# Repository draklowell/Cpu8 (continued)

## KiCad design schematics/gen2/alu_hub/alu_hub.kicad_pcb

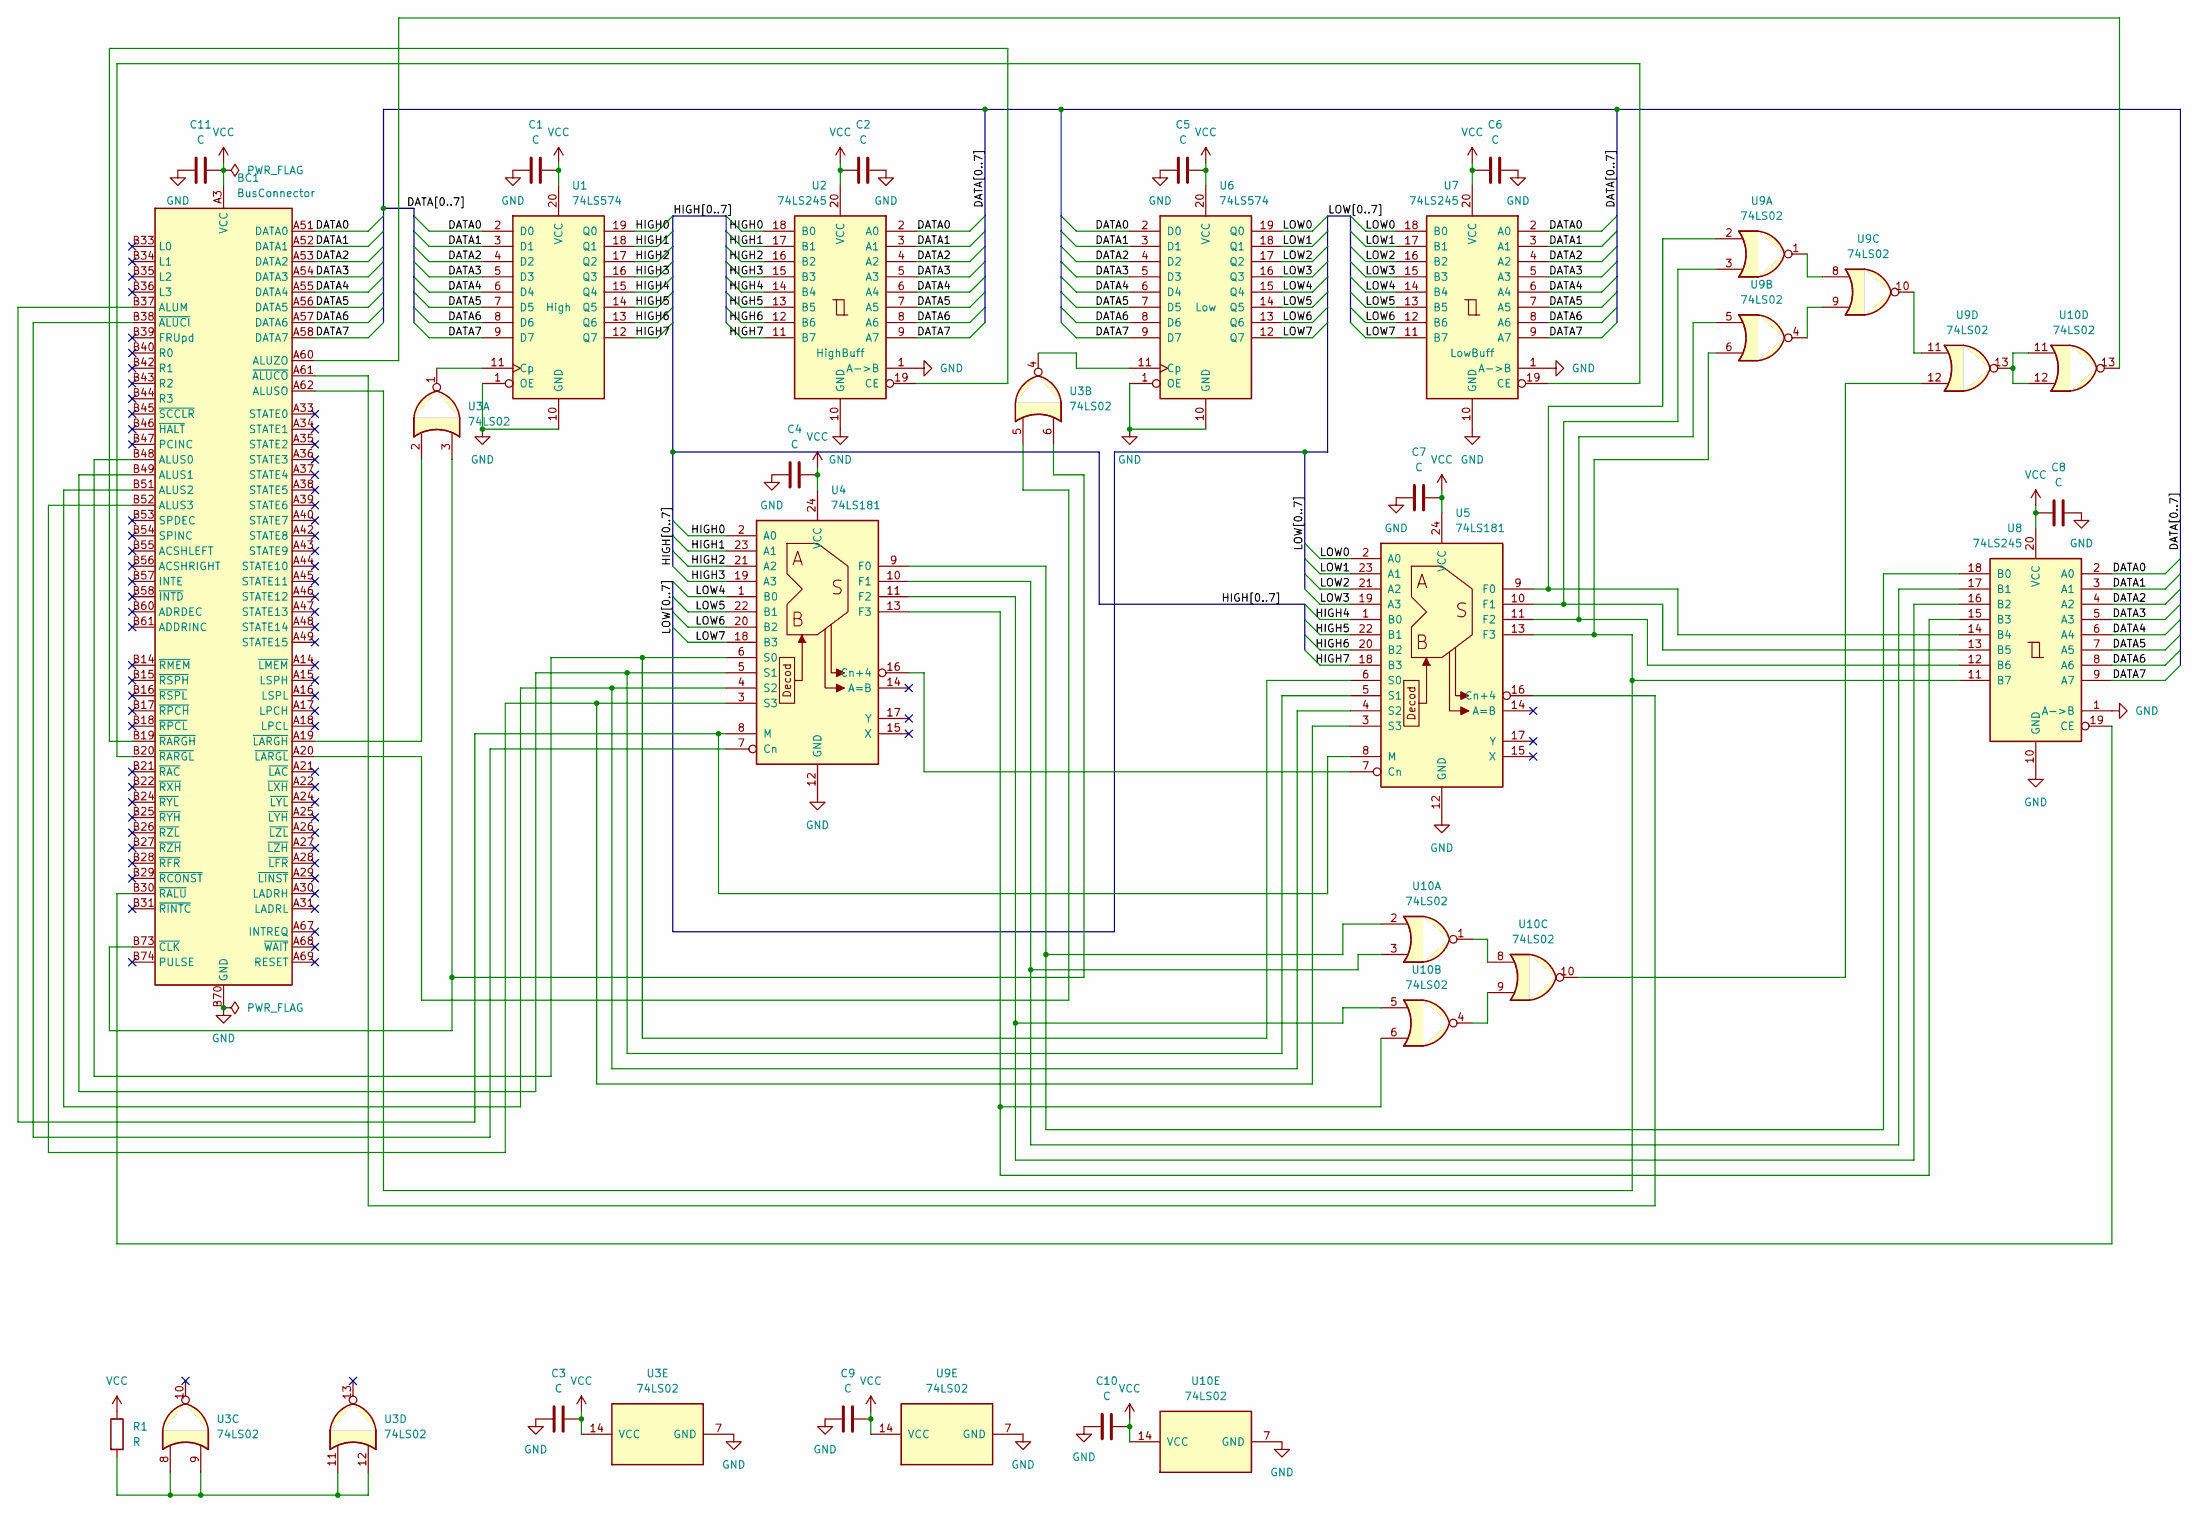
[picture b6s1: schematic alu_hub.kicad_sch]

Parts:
BC1: BusConnector; BUS_PCIexpress_x16
C1, C2, C3, C5, C6, C7, C8, C9, C10: C; C_Disc_D3.0mm_W1.6mm_P2.50mm
C4: C; C_Disc_D5.0mm_W2.5mm_P5.00mm
C11: C; C_Radial_D6.3mm_H5.0mm_P2.50mm
R1: R; R_Axial_DIN0207_L6.3mm_D2.5mm_P7.62mm_Horizontal
U1, U6: 74LS574; DIP-20_W7.62mm_Socket_LongPads
U2, U7, U8: 74LS245; DIP-20_W7.62mm_Socket_LongPads
U3, U9, U10: 74LS02; DIP-14_W7.62mm_Socket_LongPads
U4, U5: 74LS181; DIP-24_W15.24mm_Socket_LongPads

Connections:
/DATA0: BC1.A51 (DATA0), U1.2 (D0), U2.2 (A0), U6.2 (D0), U7.2 (A0), U8.2 (A0)
/DATA1: BC1.A52 (DATA1), U1.3 (D1), U2.3 (A1), U6.3 (D1), U7.3 (A1), U8.3 (A1)
/DATA2: BC1.A53 (DATA2), U1.4 (D2), U2.4 (A2), U6.4 (D2), U7.4 (A2), U8.4 (A2)
/DATA3: BC1.A54 (DATA3), U1.5 (D3), U2.5 (A3), U6.5 (D3), U7.5 (A3), U8.5 (A3)
/DATA4: BC1.A55 (DATA4), U1.6 (D4), U2.6 (A4), U6.6 (D4), U7.6 (A4), U8.6 (A4)
/DATA5: BC1.A56 (DATA5), U1.7 (D5), U2.7 (A5), U6.7 (D5), U7.7 (A5), U8.7 (A5)
/DATA6: BC1.A57 (DATA6), U1.8 (D6), U2.8 (A6), U6.8 (D6), U7.8 (A6), U8.8 (A6)
/DATA7: BC1.A58 (DATA7), U1.9 (D7), U2.9 (A7), U6.9 (D7), U7.9 (A7), U8.9 (A7)
/HIGH0: U1.19 (Q0), U2.18 (B0), U4.2 (A0)
/HIGH1: U1.18 (Q1), U2.17 (B1), U4.23 (A1)
/HIGH2: U1.17 (Q2), U2.16 (B2), U4.21 (A2)
/HIGH3: U1.16 (Q3), U2.15 (B3), U4.19 (A3)
/HIGH4: U1.15 (Q4), U2.14 (B4), U5.1 (B0)
/HIGH5: U1.14 (Q5), U2.13 (B5), U5.22 (B1)
/HIGH6: U1.13 (Q6), U2.12 (B6), U5.20 (B2)
/HIGH7: U1.12 (Q7), U2.11 (B7), U5.18 (B3)
/LOW0: U5.2 (A0), U6.19 (Q0), U7.18 (B0)
/LOW1: U5.23 (A1), U6.18 (Q1), U7.17 (B1)
/LOW2: U5.21 (A2), U6.17 (Q2), U7.16 (B2)
/LOW3: U5.19 (A3), U6.16 (Q3), U7.15 (B3)
/LOW4: U4.1 (B0), U6.15 (Q4), U7.14 (B4)
/LOW5: U4.22 (B1), U6.14 (Q5), U7.13 (B5)
/LOW6: U4.20 (B2), U6.13 (Q6), U7.12 (B6)
/LOW7: U4.18 (B3), U6.12 (Q7), U7.11 (B7)
GND: BC1.A12 (GND), BC1.A13 (GND), BC1.A23 (GND), BC1.A32 (GND), BC1.A41 (GND), BC1.A50 (GND), BC1.A59 (GND), BC1.A63 (GND), BC1.A64 (GND), BC1.A65 (GND), BC1.A66 (GND), BC1.A70 (GND), BC1.A71 (GND), BC1.A72 (GND), BC1.A73 (GND), BC1.A74 (GND), BC1.A75 (GND), BC1.A76 (GND), BC1.B12 (GND), BC1.B13 (GND), BC1.B23 (GND), BC1.B32 (GND), BC1.B41 (GND), BC1.B50 (GND), BC1.B59 (GND), BC1.B62 (GND), BC1.B63 (GND), BC1.B64 (GND), BC1.B65 (GND), BC1.B66 (GND), BC1.B67 (GND), BC1.B68 (GND), BC1.B69 (GND), BC1.B70 (GND), BC1.B71 (GND), BC1.B72 (GND), BC1.B75 (GND), BC1.B76 (GND), C1.1, C2.1, C3.1, C4.1, C5.1, C6.1, C7.1, C8.1, C9.1, C10.1, C11.1, U1.1 (OE), U1.10 (GND), U2.1 (A->B), U2.10 (GND), U3.7 (GND), U4.12 (GND), U5.12 (GND), U6.1 (OE), U6.10 (GND), U7.1 (A->B), U7.10 (GND), U8.1 (A->B), U8.10 (GND), U9.7 (GND), U10.7 (GND)
unnamed: BC1.B37 (ALUM), U4.8 (M), U5.8 (M)
unnamed: BC1.B48 (ALUS0), U4.6 (S0), U5.6 (S0)
unnamed: BC1.B49 (ALUS1), U4.5 (S1), U5.5 (S1)
unnamed: BC1.B51 (ALUS2), U4.4 (S2), U5.4 (S2)
unnamed: BC1.B52 (ALUS3), U4.3 (S3), U5.3 (S3)
unnamed: BC1.A62 (ALUSO), U5.13 (F3), U8.11 (B7), U9.6
unnamed: BC1.A60 (ALUZO), U10.13
unnamed: BC1.B38 (~ALUCI), U4.7 (Cn)
unnamed: BC1.A61 (~ALUCO), U5.16 (Cn+4)
unnamed: BC1.B73 (~CLK), U3.3, U3.6
unnamed: BC1.A19 (~LARGH), U3.2
unnamed: BC1.A20 (~LARGL), U3.5
unnamed: BC1.B30 (~RALU), U8.19 (CE)
unnamed: BC1.B19 (~RARGH), U2.19 (CE)
unnamed: BC1.B20 (~RARGL), U7.19 (CE)
unnamed: R1.2, U3.8, U3.9, U3.11, U3.12
unnamed: U1.11 (Cp), U3.1
unnamed: U4.16 (Cn+4), U5.7 (Cn)
unnamed: U4.9 (F0), U8.18 (B0), U10.2
unnamed: U4.10 (F1), U8.17 (B1), U10.3
unnamed: U4.11 (F2), U8.16 (B2), U10.5
unnamed: U4.13 (F3), U8.15 (B3), U10.6
unnamed: U5.9 (F0), U8.14 (B4), U9.2
unnamed: U5.10 (F1), U8.13 (B5), U9.3
unnamed: U5.11 (F2), U8.12 (B6), U9.5
unnamed: U3.4, U6.11 (Cp)
unnamed: U9.1, U9.8
unnamed: U9.4, U9.9
unnamed: U9.10, U9.11
unnamed: U10.1, U10.8
unnamed: U10.4, U10.9
unnamed: U9.12, U10.10
unnamed: U9.13, U10.11, U10.12
VCC: BC1.A1 (VCC), BC1.A2 (VCC), BC1.A3 (VCC), BC1.A4 (VCC), BC1.A5 (VCC), BC1.B1 (VCC), BC1.B2 (VCC), BC1.B3 (VCC), BC1.B4 (VCC), BC1.B5 (VCC), C1.2, C2.2, C3.2, C4.2, C5.2, C6.2, C7.2, C8.2, C9.2, C10.2, C11.2, R1.1, U1.20 (VCC), U2.20 (VCC), U3.14 (VCC), U4.24 (VCC), U5.24 (VCC), U6.20 (VCC), U7.20 (VCC), U8.20 (VCC), U9.14 (VCC), U10.14 (VCC)

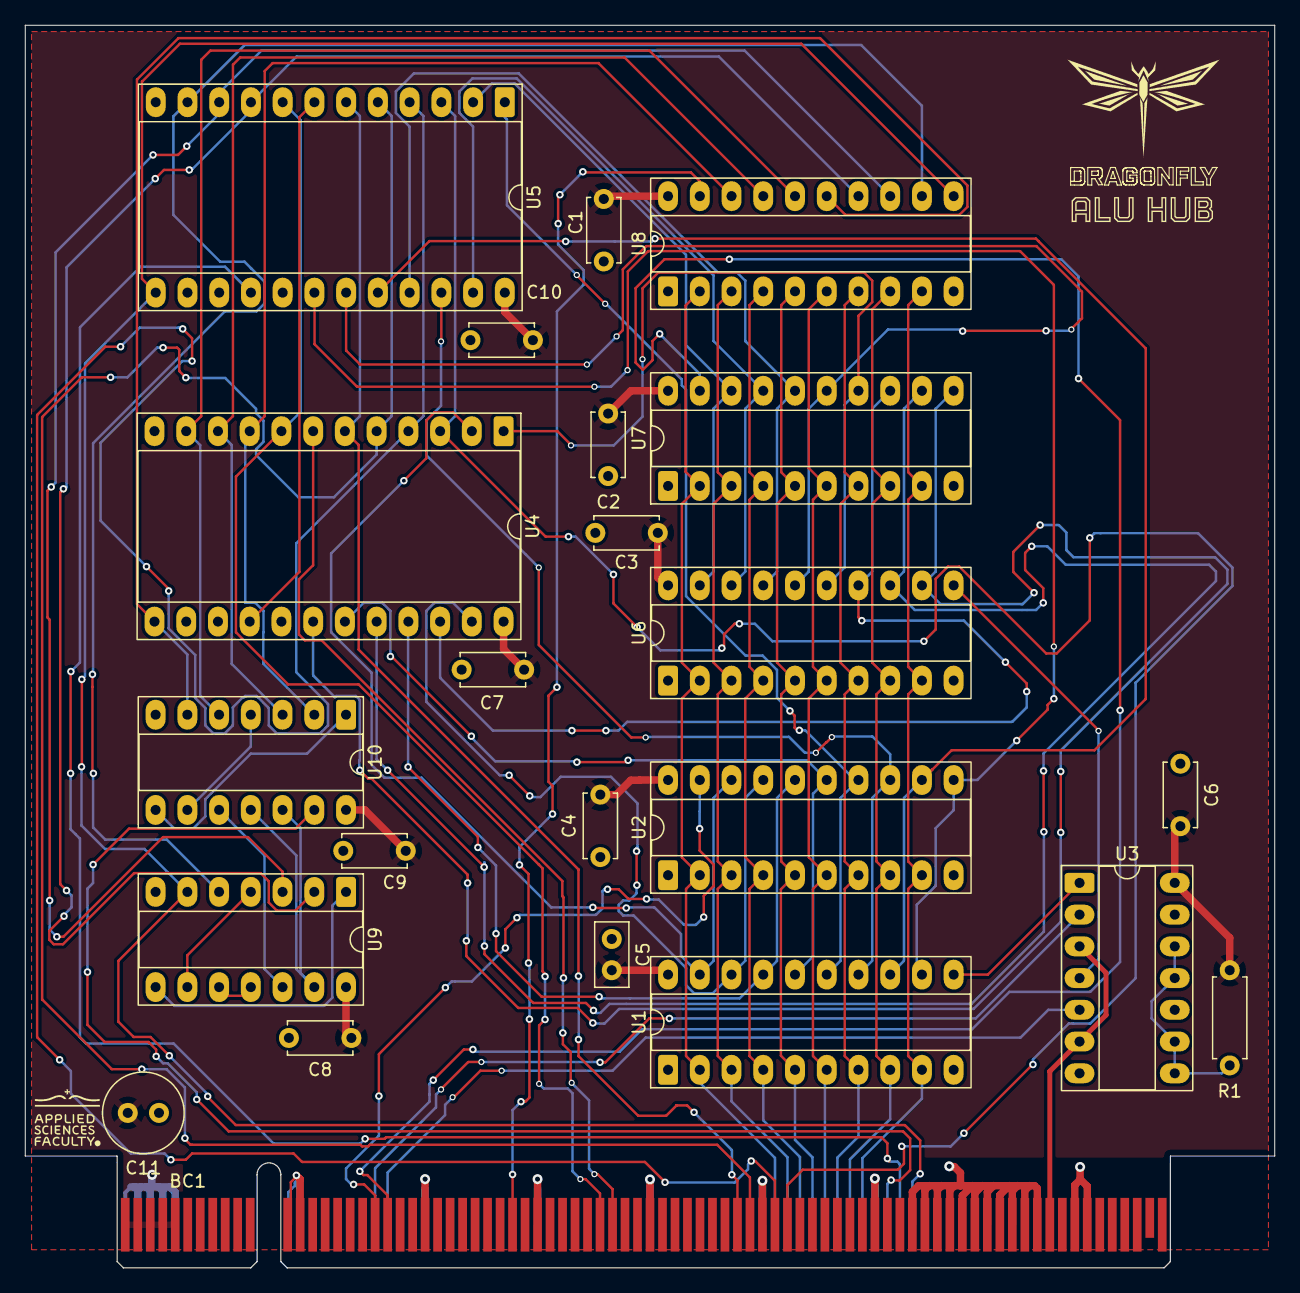
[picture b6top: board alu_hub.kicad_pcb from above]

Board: 2 copper layers, 100.0 x 99.4 mm, 24 parts (0 on the bottom side), 59 nets.

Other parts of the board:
kibuzzard-6911C7CA: G***; kibuzzard-6911C7CA

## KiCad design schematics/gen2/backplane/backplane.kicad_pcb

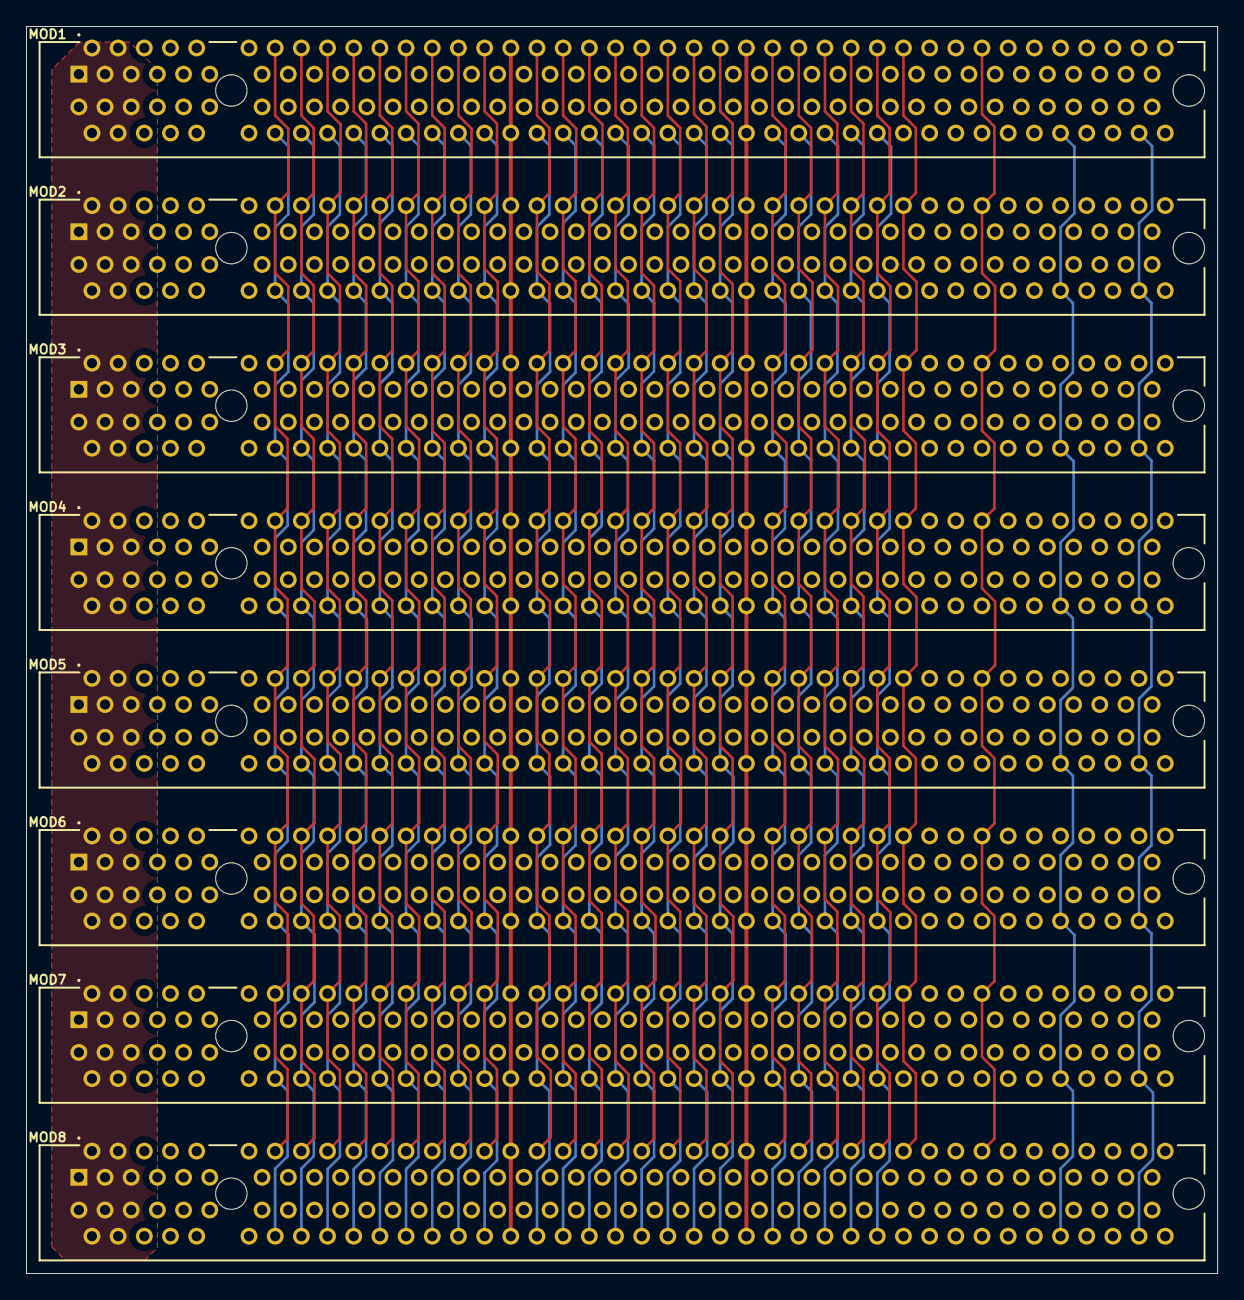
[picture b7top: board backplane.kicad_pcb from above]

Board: 4 copper layers, 91.0 x 95.3 mm, 8 parts (0 on the bottom side), 97 nets.

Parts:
MOD1, MOD2, MOD3, MOD4, MOD5, MOD6, MOD7, MOD8: Module; BusSlot

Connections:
/ACSHLEFT: MOD1.B55 (ACSHLEFT), MOD2.B55 (ACSHLEFT), MOD3.B55 (ACSHLEFT), MOD4.B55 (ACSHLEFT), MOD5.B55 (ACSHLEFT), MOD6.B55 (ACSHLEFT), MOD7.B55 (ACSHLEFT), MOD8.B55 (ACSHLEFT)
/ACSHRIGHT: MOD1.B56 (ACSHRIGHT), MOD2.B56 (ACSHRIGHT), MOD3.B56 (ACSHRIGHT), MOD4.B56 (ACSHRIGHT), MOD5.B56 (ACSHRIGHT), MOD6.B56 (ACSHRIGHT), MOD7.B56 (ACSHRIGHT), MOD8.B56 (ACSHRIGHT)
/ADRDEC: MOD1.B60 (ADRDEC), MOD2.B60 (ADRDEC), MOD3.B60 (ADRDEC), MOD4.B60 (ADRDEC), MOD5.B60 (ADRDEC), MOD6.B60 (ADRDEC), MOD7.B60 (ADRDEC), MOD8.B60 (ADRDEC)
/ADRINC: MOD1.B61 (ADDRINC), MOD2.B61 (ADDRINC), MOD3.B61 (ADDRINC), MOD4.B61 (ADDRINC), MOD5.B61 (ADDRINC), MOD6.B61 (ADDRINC), MOD7.B61 (ADDRINC), MOD8.B61 (ADDRINC)
/ALUM: MOD1.B37 (ALUM), MOD2.B37 (ALUM), MOD3.B37 (ALUM), MOD4.B37 (ALUM), MOD5.B37 (ALUM), MOD6.B37 (ALUM), MOD7.B37 (ALUM), MOD8.B37 (ALUM)
/ALUS0: MOD1.B48 (ALUS0), MOD2.B48 (ALUS0), MOD3.B48 (ALUS0), MOD4.B48 (ALUS0), MOD5.B48 (ALUS0), MOD6.B48 (ALUS0), MOD7.B48 (ALUS0), MOD8.B48 (ALUS0)
/ALUS1: MOD1.B49 (ALUS1), MOD2.B49 (ALUS1), MOD3.B49 (ALUS1), MOD4.B49 (ALUS1), MOD5.B49 (ALUS1), MOD6.B49 (ALUS1), MOD7.B49 (ALUS1), MOD8.B49 (ALUS1)
/ALUS2: MOD1.B51 (ALUS2), MOD2.B51 (ALUS2), MOD3.B51 (ALUS2), MOD4.B51 (ALUS2), MOD5.B51 (ALUS2), MOD6.B51 (ALUS2), MOD7.B51 (ALUS2), MOD8.B51 (ALUS2)
/ALUS3: MOD1.B52 (ALUS3), MOD2.B52 (ALUS3), MOD3.B52 (ALUS3), MOD4.B52 (ALUS3), MOD5.B52 (ALUS3), MOD6.B52 (ALUS3), MOD7.B52 (ALUS3), MOD8.B52 (ALUS3)
/ALUSO: MOD1.A62 (ALUSO), MOD2.A62 (ALUSO), MOD3.A62 (ALUSO), MOD4.A62 (ALUSO), MOD5.A62 (ALUSO), MOD6.A62 (ALUSO), MOD7.A62 (ALUSO), MOD8.A62 (ALUSO)
/ALUZO: MOD1.A60 (ALUZO), MOD2.A60 (ALUZO), MOD3.A60 (ALUZO), MOD4.A60 (ALUZO), MOD5.A60 (ALUZO), MOD6.A60 (ALUZO), MOD7.A60 (ALUZO), MOD8.A60 (ALUZO)
/DATA0: MOD1.A51 (DATA0), MOD2.A51 (DATA0), MOD3.A51 (DATA0), MOD4.A51 (DATA0), MOD5.A51 (DATA0), MOD6.A51 (DATA0), MOD7.A51 (DATA0), MOD8.A51 (DATA0)
/DATA1: MOD1.A52 (DATA1), MOD2.A52 (DATA1), MOD3.A52 (DATA1), MOD4.A52 (DATA1), MOD5.A52 (DATA1), MOD6.A52 (DATA1), MOD7.A52 (DATA1), MOD8.A52 (DATA1)
/DATA2: MOD1.A53 (DATA2), MOD2.A53 (DATA2), MOD3.A53 (DATA2), MOD4.A53 (DATA2), MOD5.A53 (DATA2), MOD6.A53 (DATA2), MOD7.A53 (DATA2), MOD8.A53 (DATA2)
/DATA3: MOD1.A54 (DATA3), MOD2.A54 (DATA3), MOD3.A54 (DATA3), MOD4.A54 (DATA3), MOD5.A54 (DATA3), MOD6.A54 (DATA3), MOD7.A54 (DATA3), MOD8.A54 (DATA3)
/DATA4: MOD1.A55 (DATA4), MOD2.A55 (DATA4), MOD3.A55 (DATA4), MOD4.A55 (DATA4), MOD5.A55 (DATA4), MOD6.A55 (DATA4), MOD7.A55 (DATA4), MOD8.A55 (DATA4)
/DATA5: MOD1.A56 (DATA5), MOD2.A56 (DATA5), MOD3.A56 (DATA5), MOD4.A56 (DATA5), MOD5.A56 (DATA5), MOD6.A56 (DATA5), MOD7.A56 (DATA5), MOD8.A56 (DATA5)
/DATA6: MOD1.A57 (DATA6), MOD2.A57 (DATA6), MOD3.A57 (DATA6), MOD4.A57 (DATA6), MOD5.A57 (DATA6), MOD6.A57 (DATA6), MOD7.A57 (DATA6), MOD8.A57 (DATA6)
/DATA7: MOD1.A58 (DATA7), MOD2.A58 (DATA7), MOD3.A58 (DATA7), MOD4.A58 (DATA7), MOD5.A58 (DATA7), MOD6.A58 (DATA7), MOD7.A58 (DATA7), MOD8.A58 (DATA7)
/FRUpd: MOD1.B39 (FRUpd), MOD2.B39 (FRUpd), MOD3.B39 (FRUpd), MOD4.B39 (FRUpd), MOD5.B39 (FRUpd), MOD6.B39 (FRUpd), MOD7.B39 (FRUpd), MOD8.B39 (FRUpd)
/INTE: MOD1.B57 (INTE), MOD2.B57 (INTE), MOD3.B57 (INTE), MOD4.B57 (INTE), MOD5.B57 (INTE), MOD6.B57 (INTE), MOD7.B57 (INTE), MOD8.B57 (INTE)
/INTREQ: MOD1.A67 (INTREQ), MOD2.A67 (INTREQ), MOD3.A67 (INTREQ), MOD4.A67 (INTREQ), MOD5.A67 (INTREQ), MOD6.A67 (INTREQ), MOD7.A67 (INTREQ), MOD8.A67 (INTREQ)
/L0: MOD1.B33 (L0), MOD2.B33 (L0), MOD3.B33 (L0), MOD4.B33 (L0), MOD5.B33 (L0), MOD6.B33 (L0), MOD7.B33 (L0), MOD8.B33 (L0)
/L1: MOD1.B34 (L1), MOD2.B34 (L1), MOD3.B34 (L1), MOD4.B34 (L1), MOD5.B34 (L1), MOD6.B34 (L1), MOD7.B34 (L1), MOD8.B34 (L1)
/L2: MOD1.B35 (L2), MOD2.B35 (L2), MOD3.B35 (L2), MOD4.B35 (L2), MOD5.B35 (L2), MOD6.B35 (L2), MOD7.B35 (L2), MOD8.B35 (L2)
/L3: MOD1.B36 (L3), MOD2.B36 (L3), MOD3.B36 (L3), MOD4.B36 (L3), MOD5.B36 (L3), MOD6.B36 (L3), MOD7.B36 (L3), MOD8.B36 (L3)
/L4: MOD1.B79 (L4), MOD2.B79 (L4), MOD3.B79 (L4), MOD4.B79 (L4), MOD5.B79 (L4), MOD6.B79 (L4), MOD7.B79 (L4), MOD8.B79 (L4)
/LADRH: MOD1.A30 (LADRH), MOD2.A30 (LADRH), MOD3.A30 (LADRH), MOD4.A30 (LADRH), MOD5.A30 (LADRH), MOD6.A30 (LADRH), MOD7.A30 (LADRH), MOD8.A30 (LADRH)
/LADRL: MOD1.A31 (LADRL), MOD2.A31 (LADRL), MOD3.A31 (LADRL), MOD4.A31 (LADRL), MOD5.A31 (LADRL), MOD6.A31 (LADRL), MOD7.A31 (LADRL), MOD8.A31 (LADRL)
/LPCH: MOD1.A17 (LPCH), MOD2.A17 (LPCH), MOD3.A17 (LPCH), MOD4.A17 (LPCH), MOD5.A17 (LPCH), MOD6.A17 (LPCH), MOD7.A17 (LPCH), MOD8.A17 (LPCH)
/LPCL: MOD1.A18 (LPCL), MOD2.A18 (LPCL), MOD3.A18 (LPCL), MOD4.A18 (LPCL), MOD5.A18 (LPCL), MOD6.A18 (LPCL), MOD7.A18 (LPCL), MOD8.A18 (LPCL)
/LSPH: MOD1.A15 (LSPH), MOD2.A15 (LSPH), MOD3.A15 (LSPH), MOD4.A15 (LSPH), MOD5.A15 (LSPH), MOD6.A15 (LSPH), MOD7.A15 (LSPH), MOD8.A15 (LSPH)
/LSPL: MOD1.A16 (LSPL), MOD2.A16 (LSPL), MOD3.A16 (LSPL), MOD4.A16 (LSPL), MOD5.A16 (LSPL), MOD6.A16 (LSPL), MOD7.A16 (LSPL), MOD8.A16 (LSPL)
/PCINC: MOD1.B47 (PCINC), MOD2.B47 (PCINC), MOD3.B47 (PCINC), MOD4.B47 (PCINC), MOD5.B47 (PCINC), MOD6.B47 (PCINC), MOD7.B47 (PCINC), MOD8.B47 (PCINC)
/PULSE: MOD1.B74 (PULSE), MOD2.B74 (PULSE), MOD3.B74 (PULSE), MOD4.B74 (PULSE), MOD5.B74 (PULSE), MOD6.B74 (PULSE), MOD7.B74 (PULSE), MOD8.B74 (PULSE)
/R0: MOD1.B40 (R0), MOD2.B40 (R0), MOD3.B40 (R0), MOD4.B40 (R0), MOD5.B40 (R0), MOD6.B40 (R0), MOD7.B40 (R0), MOD8.B40 (R0)
/R1: MOD1.B42 (R1), MOD2.B42 (R1), MOD3.B42 (R1), MOD4.B42 (R1), MOD5.B42 (R1), MOD6.B42 (R1), MOD7.B42 (R1), MOD8.B42 (R1)
/R2: MOD1.B43 (R2), MOD2.B43 (R2), MOD3.B43 (R2), MOD4.B43 (R2), MOD5.B43 (R2), MOD6.B43 (R2), MOD7.B43 (R2), MOD8.B43 (R2)
/R3: MOD1.B44 (R3), MOD2.B44 (R3), MOD3.B44 (R3), MOD4.B44 (R3), MOD5.B44 (R3), MOD6.B44 (R3), MOD7.B44 (R3), MOD8.B44 (R3)
/R4: MOD1.B80 (R4), MOD2.B80 (R4), MOD3.B80 (R4), MOD4.B80 (R4), MOD5.B80 (R4), MOD6.B80 (R4), MOD7.B80 (R4), MOD8.B80 (R4)
/RESET: MOD1.A69 (RESET), MOD2.A69 (RESET), MOD3.A69 (RESET), MOD4.A69 (RESET), MOD5.A69 (RESET), MOD6.A69 (RESET), MOD7.A69 (RESET), MOD8.A69 (RESET)
/SPDEC: MOD1.B53 (SPDEC), MOD2.B53 (SPDEC), MOD3.B53 (SPDEC), MOD4.B53 (SPDEC), MOD5.B53 (SPDEC), MOD6.B53 (SPDEC), MOD7.B53 (SPDEC), MOD8.B53 (SPDEC)
/SPINC: MOD1.B54 (SPINC), MOD2.B54 (SPINC), MOD3.B54 (SPINC), MOD4.B54 (SPINC), MOD5.B54 (SPINC), MOD6.B54 (SPINC), MOD7.B54 (SPINC), MOD8.B54 (SPINC)
/STATE0: MOD1.A33 (STATE0), MOD2.A33 (STATE0), MOD3.A33 (STATE0), MOD4.A33 (STATE0), MOD5.A33 (STATE0), MOD6.A33 (STATE0), MOD7.A33 (STATE0), MOD8.A33 (STATE0)
/STATE1: MOD1.A34 (STATE1), MOD2.A34 (STATE1), MOD3.A34 (STATE1), MOD4.A34 (STATE1), MOD5.A34 (STATE1), MOD6.A34 (STATE1), MOD7.A34 (STATE1), MOD8.A34 (STATE1)
/STATE2: MOD1.A35 (STATE2), MOD2.A35 (STATE2), MOD3.A35 (STATE2), MOD4.A35 (STATE2), MOD5.A35 (STATE2), MOD6.A35 (STATE2), MOD7.A35 (STATE2), MOD8.A35 (STATE2)
/STATE3: MOD1.A36 (STATE3), MOD2.A36 (STATE3), MOD3.A36 (STATE3), MOD4.A36 (STATE3), MOD5.A36 (STATE3), MOD6.A36 (STATE3), MOD7.A36 (STATE3), MOD8.A36 (STATE3)
/STATE4: MOD1.A37 (STATE4), MOD2.A37 (STATE4), MOD3.A37 (STATE4), MOD4.A37 (STATE4), MOD5.A37 (STATE4), MOD6.A37 (STATE4), MOD7.A37 (STATE4), MOD8.A37 (STATE4)
/STATE5: MOD1.A38 (STATE5), MOD2.A38 (STATE5), MOD3.A38 (STATE5), MOD4.A38 (STATE5), MOD5.A38 (STATE5), MOD6.A38 (STATE5), MOD7.A38 (STATE5), MOD8.A38 (STATE5)
/STATE6: MOD1.A39 (STATE6), MOD2.A39 (STATE6), MOD3.A39 (STATE6), MOD4.A39 (STATE6), MOD5.A39 (STATE6), MOD6.A39 (STATE6), MOD7.A39 (STATE6), MOD8.A39 (STATE6)
/STATE7: MOD1.A40 (STATE7), MOD2.A40 (STATE7), MOD3.A40 (STATE7), MOD4.A40 (STATE7), MOD5.A40 (STATE7), MOD6.A40 (STATE7), MOD7.A40 (STATE7), MOD8.A40 (STATE7)
/STATE8: MOD1.A42 (STATE8), MOD2.A42 (STATE8), MOD3.A42 (STATE8), MOD4.A42 (STATE8), MOD5.A42 (STATE8), MOD6.A42 (STATE8), MOD7.A42 (STATE8), MOD8.A42 (STATE8)
/STATE9: MOD1.A43 (STATE9), MOD2.A43 (STATE9), MOD3.A43 (STATE9), MOD4.A43 (STATE9), MOD5.A43 (STATE9), MOD6.A43 (STATE9), MOD7.A43 (STATE9), MOD8.A43 (STATE9)
/STATE10: MOD1.A44 (STATE10), MOD2.A44 (STATE10), MOD3.A44 (STATE10), MOD4.A44 (STATE10), MOD5.A44 (STATE10), MOD6.A44 (STATE10), MOD7.A44 (STATE10), MOD8.A44 (STATE10)
/STATE11: MOD1.A45 (STATE11), MOD2.A45 (STATE11), MOD3.A45 (STATE11), MOD4.A45 (STATE11), MOD5.A45 (STATE11), MOD6.A45 (STATE11), MOD7.A45 (STATE11), MOD8.A45 (STATE11)
/STATE12: MOD1.A46 (STATE12), MOD2.A46 (STATE12), MOD3.A46 (STATE12), MOD4.A46 (STATE12), MOD5.A46 (STATE12), MOD6.A46 (STATE12), MOD7.A46 (STATE12), MOD8.A46 (STATE12)
/STATE13: MOD1.A47 (STATE13), MOD2.A47 (STATE13), MOD3.A47 (STATE13), MOD4.A47 (STATE13), MOD5.A47 (STATE13), MOD6.A47 (STATE13), MOD7.A47 (STATE13), MOD8.A47 (STATE13)
/STATE14: MOD1.A48 (STATE14), MOD2.A48 (STATE14), MOD3.A48 (STATE14), MOD4.A48 (STATE14), MOD5.A48 (STATE14), MOD6.A48 (STATE14), MOD7.A48 (STATE14), MOD8.A48 (STATE14)
/STATE15: MOD1.A49 (STATE15), MOD2.A49 (STATE15), MOD3.A49 (STATE15), MOD4.A49 (STATE15), MOD5.A49 (STATE15), MOD6.A49 (STATE15), MOD7.A49 (STATE15), MOD8.A49 (STATE15)
/STATE16: MOD1.A79 (STATE16), MOD2.A79 (STATE16), MOD3.A79 (STATE16), MOD4.A79 (STATE16), MOD5.A79 (STATE16), MOD6.A79 (STATE16), MOD7.A79 (STATE16), MOD8.A79 (STATE16)
/~ALUCI: MOD1.B38 (~ALUCI), MOD2.B38 (~ALUCI), MOD3.B38 (~ALUCI), MOD4.B38 (~ALUCI), MOD5.B38 (~ALUCI), MOD6.B38 (~ALUCI), MOD7.B38 (~ALUCI), MOD8.B38 (~ALUCI)
/~ALUCO: MOD1.A61 (~ALUCO), MOD2.A61 (~ALUCO), MOD3.A61 (~ALUCO), MOD4.A61 (~ALUCO), MOD5.A61 (~ALUCO), MOD6.A61 (~ALUCO), MOD7.A61 (~ALUCO), MOD8.A61 (~ALUCO)
/~CLK: MOD1.B73 (~CLK), MOD2.B73 (~CLK), MOD3.B73 (~CLK), MOD4.B73 (~CLK), MOD5.B73 (~CLK), MOD6.B73 (~CLK), MOD7.B73 (~CLK), MOD8.B73 (~CLK)
/~HALT: MOD1.B46 (~HALT), MOD2.B46 (~HALT), MOD3.B46 (~HALT), MOD4.B46 (~HALT), MOD5.B46 (~HALT), MOD6.B46 (~HALT), MOD7.B46 (~HALT), MOD8.B46 (~HALT)
/~INTD: MOD1.B58 (~INTD), MOD2.B58 (~INTD), MOD3.B58 (~INTD), MOD4.B58 (~INTD), MOD5.B58 (~INTD), MOD6.B58 (~INTD), MOD7.B58 (~INTD), MOD8.B58 (~INTD)
/~LAC: MOD1.A21 (~LAC), MOD2.A21 (~LAC), MOD3.A21 (~LAC), MOD4.A21 (~LAC), MOD5.A21 (~LAC), MOD6.A21 (~LAC), MOD7.A21 (~LAC), MOD8.A21 (~LAC)
/~LARGH: MOD1.A19 (~LARGH), MOD2.A19 (~LARGH), MOD3.A19 (~LARGH), MOD4.A19 (~LARGH), MOD5.A19 (~LARGH), MOD6.A19 (~LARGH), MOD7.A19 (~LARGH), MOD8.A19 (~LARGH)
/~LARGL: MOD1.A20 (~LARGL), MOD2.A20 (~LARGL), MOD3.A20 (~LARGL), MOD4.A20 (~LARGL), MOD5.A20 (~LARGL), MOD6.A20 (~LARGL), MOD7.A20 (~LARGL), MOD8.A20 (~LARGL)
/~LFR: MOD1.A28 (~LFR), MOD2.A28 (~LFR), MOD3.A28 (~LFR), MOD4.A28 (~LFR), MOD5.A28 (~LFR), MOD6.A28 (~LFR), MOD7.A28 (~LFR), MOD8.A28 (~LFR)
/~LINST: MOD1.A29 (~LINST), MOD2.A29 (~LINST), MOD3.A29 (~LINST), MOD4.A29 (~LINST), MOD5.A29 (~LINST), MOD6.A29 (~LINST), MOD7.A29 (~LINST), MOD8.A29 (~LINST)
/~LMEM: MOD1.A14 (~LMEM), MOD2.A14 (~LMEM), MOD3.A14 (~LMEM), MOD4.A14 (~LMEM), MOD5.A14 (~LMEM), MOD6.A14 (~LMEM), MOD7.A14 (~LMEM), MOD8.A14 (~LMEM)
/~LXH: MOD1.A22 (~LXH), MOD2.A22 (~LXH), MOD3.A22 (~LXH), MOD4.A22 (~LXH), MOD5.A22 (~LXH), MOD6.A22 (~LXH), MOD7.A22 (~LXH), MOD8.A22 (~LXH)
/~LYH: MOD1.A25 (~LYH), MOD2.A25 (~LYH), MOD3.A25 (~LYH), MOD4.A25 (~LYH), MOD5.A25 (~LYH), MOD6.A25 (~LYH), MOD7.A25 (~LYH), MOD8.A25 (~LYH)
/~LYL: MOD1.A24 (~LYL), MOD2.A24 (~LYL), MOD3.A24 (~LYL), MOD4.A24 (~LYL), MOD5.A24 (~LYL), MOD6.A24 (~LYL), MOD7.A24 (~LYL), MOD8.A24 (~LYL)
/~LZH: MOD1.A27 (~LZH), MOD2.A27 (~LZH), MOD3.A27 (~LZH), MOD4.A27 (~LZH), MOD5.A27 (~LZH), MOD6.A27 (~LZH), MOD7.A27 (~LZH), MOD8.A27 (~LZH)
/~LZL: MOD1.A26 (~LZL), MOD2.A26 (~LZL), MOD3.A26 (~LZL), MOD4.A26 (~LZL), MOD5.A26 (~LZL), MOD6.A26 (~LZL), MOD7.A26 (~LZL), MOD8.A26 (~LZL)
/~RAC: MOD1.B21 (~RAC), MOD2.B21 (~RAC), MOD3.B21 (~RAC), MOD4.B21 (~RAC), MOD5.B21 (~RAC), MOD6.B21 (~RAC), MOD7.B21 (~RAC), MOD8.B21 (~RAC)
/~RALU: MOD1.B30 (~RALU), MOD2.B30 (~RALU), MOD3.B30 (~RALU), MOD4.B30 (~RALU), MOD5.B30 (~RALU), MOD6.B30 (~RALU), MOD7.B30 (~RALU), MOD8.B30 (~RALU)
/~RARGH: MOD1.B19 (~RARGH), MOD2.B19 (~RARGH), MOD3.B19 (~RARGH), MOD4.B19 (~RARGH), MOD5.B19 (~RARGH), MOD6.B19 (~RARGH), MOD7.B19 (~RARGH), MOD8.B19 (~RARGH)
/~RARGL: MOD1.B20 (~RARGL), MOD2.B20 (~RARGL), MOD3.B20 (~RARGL), MOD4.B20 (~RARGL), MOD5.B20 (~RARGL), MOD6.B20 (~RARGL), MOD7.B20 (~RARGL), MOD8.B20 (~RARGL)
/~RCONST: MOD1.B29 (~RCONST), MOD2.B29 (~RCONST), MOD3.B29 (~RCONST), MOD4.B29 (~RCONST), MOD5.B29 (~RCONST), MOD6.B29 (~RCONST), MOD7.B29 (~RCONST), MOD8.B29 (~RCONST)
/~RFR: MOD1.B28 (~RFR), MOD2.B28 (~RFR), MOD3.B28 (~RFR), MOD4.B28 (~RFR), MOD5.B28 (~RFR), MOD6.B28 (~RFR), MOD7.B28 (~RFR), MOD8.B28 (~RFR)
/~RINTC: MOD1.B31 (~RINTC), MOD2.B31 (~RINTC), MOD3.B31 (~RINTC), MOD4.B31 (~RINTC), MOD5.B31 (~RINTC), MOD6.B31 (~RINTC), MOD7.B31 (~RINTC), MOD8.B31 (~RINTC)
/~RMEM: MOD1.B14 (~RMEM), MOD2.B14 (~RMEM), MOD3.B14 (~RMEM), MOD4.B14 (~RMEM), MOD5.B14 (~RMEM), MOD6.B14 (~RMEM), MOD7.B14 (~RMEM), MOD8.B14 (~RMEM)
/~RPCH: MOD1.B17 (~RPCH), MOD2.B17 (~RPCH), MOD3.B17 (~RPCH), MOD4.B17 (~RPCH), MOD5.B17 (~RPCH), MOD6.B17 (~RPCH), MOD7.B17 (~RPCH), MOD8.B17 (~RPCH)
/~RPCL: MOD1.B18 (~RPCL), MOD2.B18 (~RPCL), MOD3.B18 (~RPCL), MOD4.B18 (~RPCL), MOD5.B18 (~RPCL), MOD6.B18 (~RPCL), MOD7.B18 (~RPCL), MOD8.B18 (~RPCL)
/~RSPH: MOD1.B15 (~RSPH), MOD2.B15 (~RSPH), MOD3.B15 (~RSPH), MOD4.B15 (~RSPH), MOD5.B15 (~RSPH), MOD6.B15 (~RSPH), MOD7.B15 (~RSPH), MOD8.B15 (~RSPH)
/~RSPL: MOD1.B16 (~RSPL), MOD2.B16 (~RSPL), MOD3.B16 (~RSPL), MOD4.B16 (~RSPL), MOD5.B16 (~RSPL), MOD6.B16 (~RSPL), MOD7.B16 (~RSPL), MOD8.B16 (~RSPL)
/~RXH: MOD1.B22 (~RXH), MOD2.B22 (~RXH), MOD3.B22 (~RXH), MOD4.B22 (~RXH), MOD5.B22 (~RXH), MOD6.B22 (~RXH), MOD7.B22 (~RXH), MOD8.B22 (~RXH)
/~RYH: MOD1.B25 (~RYH), MOD2.B25 (~RYH), MOD3.B25 (~RYH), MOD4.B25 (~RYH), MOD5.B25 (~RYH), MOD6.B25 (~RYH), MOD7.B25 (~RYH), MOD8.B25 (~RYH)
/~RYL: MOD1.B24 (~RYL), MOD2.B24 (~RYL), MOD3.B24 (~RYL), MOD4.B24 (~RYL), MOD5.B24 (~RYL), MOD6.B24 (~RYL), MOD7.B24 (~RYL), MOD8.B24 (~RYL)
/~RZH: MOD1.B27 (~RZH), MOD2.B27 (~RZH), MOD3.B27 (~RZH), MOD4.B27 (~RZH), MOD5.B27 (~RZH), MOD6.B27 (~RZH), MOD7.B27 (~RZH), MOD8.B27 (~RZH)
/~RZL: MOD1.B26 (~RZL), MOD2.B26 (~RZL), MOD3.B26 (~RZL), MOD4.B26 (~RZL), MOD5.B26 (~RZL), MOD6.B26 (~RZL), MOD7.B26 (~RZL), MOD8.B26 (~RZL)
/~SCCLR: MOD1.B45 (~SCCLR), MOD2.B45 (~SCCLR), MOD3.B45 (~SCCLR), MOD4.B45 (~SCCLR), MOD5.B45 (~SCCLR), MOD6.B45 (~SCCLR), MOD7.B45 (~SCCLR), MOD8.B45 (~SCCLR)
/~WAIT: MOD1.A68 (~WAIT), MOD2.A68 (~WAIT), MOD3.A68 (~WAIT), MOD4.A68 (~WAIT), MOD5.A68 (~WAIT), MOD6.A68 (~WAIT), MOD7.A68 (~WAIT), MOD8.A68 (~WAIT)
GND: MOD1.A12 (GND), MOD1.A13 (GND), MOD1.A23 (GND), MOD1.A32 (GND), MOD1.A41 (GND), MOD1.A50 (GND), MOD1.A59 (GND), MOD1.A63 (GND), MOD1.A64 (GND), MOD1.A65 (GND), MOD1.A66 (GND), MOD1.A70 (GND), MOD1.A71 (GND), MOD1.A72 (GND), MOD1.A73 (GND), MOD1.A74 (GND), MOD1.A75 (GND), MOD1.A76 (GND), MOD1.B12 (GND), MOD1.B13 (GND), MOD1.B23 (GND), MOD1.B32 (GND), MOD1.B41 (GND), MOD1.B50 (GND), MOD1.B59 (GND), MOD1.B62 (GND), MOD1.B63 (GND), MOD1.B64 (GND), MOD1.B65 (GND), MOD1.B66 (GND), MOD1.B67 (GND), MOD1.B68 (GND), MOD1.B69 (GND), MOD1.B70 (GND), MOD1.B71 (GND), MOD1.B72 (GND), MOD1.B75 (GND), MOD1.B76 (GND), MOD2.A12 (GND), MOD2.A13 (GND), MOD2.A23 (GND), MOD2.A32 (GND), MOD2.A41 (GND), MOD2.A50 (GND), MOD2.A59 (GND), MOD2.A63 (GND), MOD2.A64 (GND), MOD2.A65 (GND), MOD2.A66 (GND), MOD2.A70 (GND), MOD2.A71 (GND), MOD2.A72 (GND), MOD2.A73 (GND), MOD2.A74 (GND), MOD2.A75 (GND), MOD2.A76 (GND), MOD2.B12 (GND), MOD2.B13 (GND), MOD2.B23 (GND), MOD2.B32 (GND), MOD2.B41 (GND), MOD2.B50 (GND), MOD2.B59 (GND), MOD2.B62 (GND), MOD2.B63 (GND), MOD2.B64 (GND), MOD2.B65 (GND), MOD2.B66 (GND), MOD2.B67 (GND), MOD2.B68 (GND), MOD2.B69 (GND), MOD2.B70 (GND), MOD2.B71 (GND), MOD2.B72 (GND), MOD2.B75 (GND), MOD2.B76 (GND), MOD3.A12 (GND), MOD3.A13 (GND), MOD3.A23 (GND), MOD3.A32 (GND), MOD3.A41 (GND), MOD3.A50 (GND), MOD3.A59 (GND), MOD3.A63 (GND), MOD3.A64 (GND), MOD3.A65 (GND), MOD3.A66 (GND), MOD3.A70 (GND), MOD3.A71 (GND), MOD3.A72 (GND), MOD3.A73 (GND), MOD3.A74 (GND), MOD3.A75 (GND), MOD3.A76 (GND), MOD3.B12 (GND), MOD3.B13 (GND), MOD3.B23 (GND), MOD3.B32 (GND), MOD3.B41 (GND), MOD3.B50 (GND), MOD3.B59 (GND), MOD3.B62 (GND), MOD3.B63 (GND), MOD3.B64 (GND), MOD3.B65 (GND), MOD3.B66 (GND), MOD3.B67 (GND), MOD3.B68 (GND), MOD3.B69 (GND), MOD3.B70 (GND), MOD3.B71 (GND), MOD3.B72 (GND), MOD3.B75 (GND), MOD3.B76 (GND), MOD4.A12 (GND), MOD4.A13 (GND), MOD4.A23 (GND), MOD4.A32 (GND), MOD4.A41 (GND), MOD4.A50 (GND), MOD4.A59 (GND), MOD4.A63 (GND), MOD4.A64 (GND), MOD4.A65 (GND), MOD4.A66 (GND), MOD4.A70 (GND), MOD4.A71 (GND), MOD4.A72 (GND), MOD4.A73 (GND), MOD4.A74 (GND), MOD4.A75 (GND), MOD4.A76 (GND), MOD4.B12 (GND), MOD4.B13 (GND), MOD4.B23 (GND), MOD4.B32 (GND), MOD4.B41 (GND), MOD4.B50 (GND), MOD4.B59 (GND), MOD4.B62 (GND), MOD4.B63 (GND), MOD4.B64 (GND), MOD4.B65 (GND), MOD4.B66 (GND), MOD4.B67 (GND), MOD4.B68 (GND), MOD4.B69 (GND), MOD4.B70 (GND), MOD4.B71 (GND), MOD4.B72 (GND), MOD4.B75 (GND), MOD4.B76 (GND), MOD5.A12 (GND), MOD5.A13 (GND), MOD5.A23 (GND), MOD5.A32 (GND), MOD5.A41 (GND), MOD5.A50 (GND), MOD5.A59 (GND), MOD5.A63 (GND), MOD5.A64 (GND), MOD5.A65 (GND), MOD5.A66 (GND), MOD5.A70 (GND), MOD5.A71 (GND), MOD5.A72 (GND), MOD5.A73 (GND), MOD5.A74 (GND), MOD5.A75 (GND), MOD5.A76 (GND), MOD5.B12 (GND), MOD5.B13 (GND), MOD5.B23 (GND), MOD5.B32 (GND), MOD5.B41 (GND), MOD5.B50 (GND), MOD5.B59 (GND), MOD5.B62 (GND), MOD5.B63 (GND), MOD5.B64 (GND), MOD5.B65 (GND), MOD5.B66 (GND), MOD5.B67 (GND), MOD5.B68 (GND), MOD5.B69 (GND), MOD5.B70 (GND), MOD5.B71 (GND), MOD5.B72 (GND), MOD5.B75 (GND), MOD5.B76 (GND), MOD6.A12 (GND), MOD6.A13 (GND), MOD6.A23 (GND), MOD6.A32 (GND), MOD6.A41 (GND), MOD6.A50 (GND), MOD6.A59 (GND), MOD6.A63 (GND), MOD6.A64 (GND), MOD6.A65 (GND), MOD6.A66 (GND), MOD6.A70 (GND), MOD6.A71 (GND), MOD6.A72 (GND), MOD6.A73 (GND), MOD6.A74 (GND), MOD6.A75 (GND), MOD6.A76 (GND), MOD6.B12 (GND), MOD6.B13 (GND), MOD6.B23 (GND), MOD6.B32 (GND), MOD6.B41 (GND), MOD6.B50 (GND), MOD6.B59 (GND), MOD6.B62 (GND), MOD6.B63 (GND), MOD6.B64 (GND), MOD6.B65 (GND), MOD6.B66 (GND), MOD6.B67 (GND), MOD6.B68 (GND), MOD6.B69 (GND), MOD6.B70 (GND), MOD6.B71 (GND), MOD6.B72 (GND), MOD6.B75 (GND), MOD6.B76 (GND), MOD7.A12 (GND), MOD7.A13 (GND), MOD7.A23 (GND), MOD7.A32 (GND), MOD7.A41 (GND), MOD7.A50 (GND), MOD7.A59 (GND), MOD7.A63 (GND), MOD7.A64 (GND), MOD7.A65 (GND), MOD7.A66 (GND), MOD7.A70 (GND), MOD7.A71 (GND), MOD7.A72 (GND), MOD7.A73 (GND), MOD7.A74 (GND), MOD7.A75 (GND), MOD7.A76 (GND), MOD7.B12 (GND), MOD7.B13 (GND), MOD7.B23 (GND), MOD7.B32 (GND), MOD7.B41 (GND), MOD7.B50 (GND), MOD7.B59 (GND), MOD7.B62 (GND), MOD7.B63 (GND), MOD7.B64 (GND), MOD7.B65 (GND), MOD7.B66 (GND), MOD7.B67 (GND), MOD7.B68 (GND), MOD7.B69 (GND), MOD7.B70 (GND), MOD7.B71 (GND), MOD7.B72 (GND), MOD7.B75 (GND), MOD7.B76 (GND), MOD8.A12 (GND), MOD8.A13 (GND), MOD8.A23 (GND), MOD8.A32 (GND), MOD8.A41 (GND), MOD8.A50 (GND), MOD8.A59 (GND), MOD8.A63 (GND), MOD8.A64 (GND), MOD8.A65 (GND), MOD8.A66 (GND), MOD8.A70 (GND), MOD8.A71 (GND), MOD8.A72 (GND), MOD8.A73 (GND), MOD8.A74 (GND), MOD8.A75 (GND), MOD8.A76 (GND), MOD8.B12 (GND), MOD8.B13 (GND), MOD8.B23 (GND), MOD8.B32 (GND), MOD8.B41 (GND), MOD8.B50 (GND), MOD8.B59 (GND), MOD8.B62 (GND), MOD8.B63 (GND), MOD8.B64 (GND), MOD8.B65 (GND), MOD8.B66 (GND), MOD8.B67 (GND), MOD8.B68 (GND), MOD8.B69 (GND), MOD8.B70 (GND), MOD8.B71 (GND), MOD8.B72 (GND), MOD8.B75 (GND), MOD8.B76 (GND)
VCC: MOD1.A1 (VCC), MOD1.A2 (VCC), MOD1.A3 (VCC), MOD1.A4 (VCC), MOD1.A5 (VCC), MOD1.B1 (VCC), MOD1.B2 (VCC), MOD1.B3 (VCC), MOD1.B4 (VCC), MOD1.B5 (VCC), MOD2.A1 (VCC), MOD2.A2 (VCC), MOD2.A3 (VCC), MOD2.A4 (VCC), MOD2.A5 (VCC), MOD2.B1 (VCC), MOD2.B2 (VCC), MOD2.B3 (VCC), MOD2.B4 (VCC), MOD2.B5 (VCC), MOD3.A1 (VCC), MOD3.A2 (VCC), MOD3.A3 (VCC), MOD3.A4 (VCC), MOD3.A5 (VCC), MOD3.B1 (VCC), MOD3.B2 (VCC), MOD3.B3 (VCC), MOD3.B4 (VCC), MOD3.B5 (VCC), MOD4.A1 (VCC), MOD4.A2 (VCC), MOD4.A3 (VCC), MOD4.A4 (VCC), MOD4.A5 (VCC), MOD4.B1 (VCC), MOD4.B2 (VCC), MOD4.B3 (VCC), MOD4.B4 (VCC), MOD4.B5 (VCC), MOD5.A1 (VCC), MOD5.A2 (VCC), MOD5.A3 (VCC), MOD5.A4 (VCC), MOD5.A5 (VCC), MOD5.B1 (VCC), MOD5.B2 (VCC), MOD5.B3 (VCC), MOD5.B4 (VCC), MOD5.B5 (VCC), MOD6.A1 (VCC), MOD6.A2 (VCC), MOD6.A3 (VCC), MOD6.A4 (VCC), MOD6.A5 (VCC), MOD6.B1 (VCC), MOD6.B2 (VCC), MOD6.B3 (VCC), MOD6.B4 (VCC), MOD6.B5 (VCC), MOD7.A1 (VCC), MOD7.A2 (VCC), MOD7.A3 (VCC), MOD7.A4 (VCC), MOD7.A5 (VCC), MOD7.B1 (VCC), MOD7.B2 (VCC), MOD7.B3 (VCC), MOD7.B4 (VCC), MOD7.B5 (VCC), MOD8.A1 (VCC), MOD8.A2 (VCC), MOD8.A3 (VCC), MOD8.A4 (VCC), MOD8.A5 (VCC), MOD8.B1 (VCC), MOD8.B2 (VCC), MOD8.B3 (VCC), MOD8.B4 (VCC), MOD8.B5 (VCC)
